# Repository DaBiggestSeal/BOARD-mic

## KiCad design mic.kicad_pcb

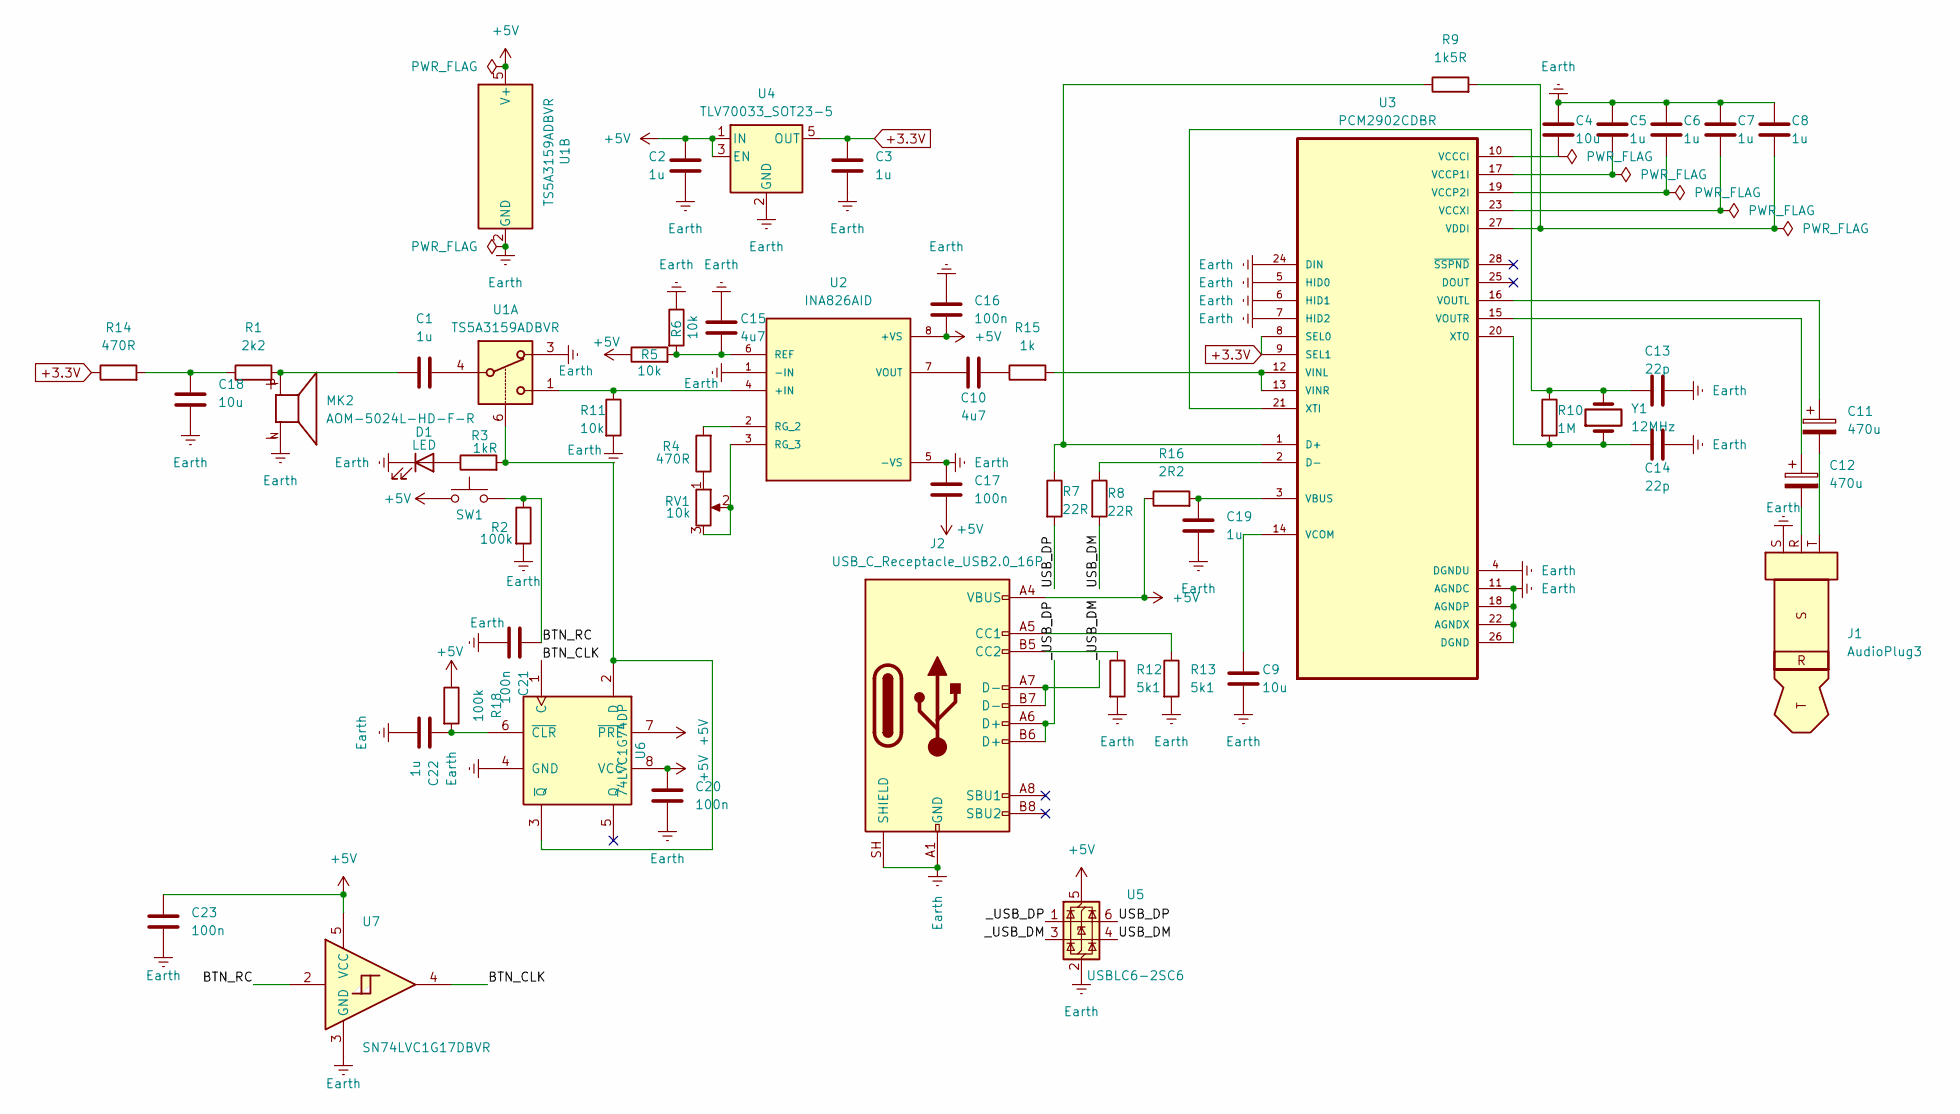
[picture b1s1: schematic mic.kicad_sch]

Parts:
C1, C2, C3, C5, C6, C7, C8, C19, C22: 1u; C_0603_1608Metric; LCSC C15849
C4, C9, C18: 10u; C_0603_1608Metric; LCSC C19702
C10, C15: 4u7; C_0603_1608Metric; LCSC C19666
C11, C12: 470u; CP_Elec_8x10; LCSC C2858857
C13, C14: 22p; C_0603_1608Metric; LCSC C1653
C16, C17, C20, C21, C23: 100n; C_0603_1608Metric; LCSC C149620
D1: LED; LED_D1.8mm_W1.8mm_H2.4mm_Horizontal_O1.27mm_Z1.6mm; LCSC C2917798
J1: AudioPlug3; Jack_3.5mm_KoreanHropartsElec_PJ-3920-3A_Vertical; LCSC C707259
J2: USB_C_Receptacle_USB2.0_16P; USB_C_Receptacle_G-Switch_GT-USB-7051x_NoA8; LCSC C2843970
MK2: AOM-5024L-HD-F-R; MIC_AOM-5024L-HD-F-R; PARTREV A; LCSC C3273730
R1: 2k2; R_0603_1608Metric; LCSC C4190
R2, R18: 100k; R_0603_1608Metric; LCSC C25803
R3: 1kR; R_0603_1608Metric; LCSC C22548
R4, R14: 470R; R_0603_1608Metric; LCSC C23179
R5, R6, R11: 10k; R_0603_1608Metric; LCSC C98220
R7, R8: 22R; R_0603_1608Metric; LCSC C23345
R9: 1k5R; R_0603_1608Metric; LCSC C22843
R10: 1M; R_0603_1608Metric; LCSC C22935
R12, R13: 5k1; R_0603_1608Metric; LCSC C23186
R15: 1k; R_0603_1608Metric; LCSC C22548
R16: 2R2; R_0603_1608Metric; LCSC C112307
RV1: 10k; Potentiometer_Alps_RK097_Single_Horizontal; LCSC C470577
SW1: SW_Push; SW_Tactile_SPST_Angled_PTS645Vx58-2LFS; LCSC alr C51018255
U1: TS5A3159ADBVR; SOT-23-6; LCSC C128405
U2: INA826AID; SOIC127P599X175-8N; PARTREV G; DigiKey_Part_Number 296-33294-5-ND
U3: PCM2902CDBR; SOP65P780X200-28N; DigiKey_Part_Number 2156-PCM2902CDBR-ND
U4: TLV70033_SOT23-5; SOT-23-5; LCSC C11337
U5: USBLC6-2SC6; SOT-23-6; LCSC C7519
U6: 74LVC1G74DP; TSSOP-8_3x3mm_P0.65mm; LCSC C548409
U7: SN74LVC1G17DBVR; SOT-23-5; LCSC C7836
Y1: 12MHz; Crystal_SMD_5032-2Pin_5.0x3.2mm; LCSC C112573

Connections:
+3.3V: C3.1, R14.1, U3.8 (SEL0), U3.9 (SEL1), U4.5 (OUT)
+5V: C2.2, C16.2, C17.2, C20.1, C23.1, J2.A4 (VBUS), J2.A9 (VBUS), J2.B4 (VBUS), J2.B9 (VBUS), R5.1, R16.1, R18.1, SW1.1, U1.5 (V+), U2.8 (+VS), U4.1 (IN), U4.3 (EN), U5.5 (VBUS), U6.7 (~PRE), U6.8 (VCC), U7.5 (VCC)
/BTN_CLK: U6.1 (C), U7.4
/BTN_RC: C21.1, R2.1, SW1.2, U7.2
/USB_DM: R8.2, U5.4 (I/O2)
/USB_DP: R7.2, U5.6 (I/O1)
/_USB_DM: J2.A7 (D-), J2.B7 (D-), U5.3 (I/O2)
/_USB_DP: J2.A6 (D+), J2.B6 (D+), U5.1 (I/O1)
Earth: C2.1, C3.2, C4.1, C5.1, C6.1, C7.1, C8.1, C9.2, C13.2, C14.2, C15.1, C16.1, C17.1, C18.2, C19.2, C20.2, C21.2, C22.2, C23.2, D1.1 (K), J1.S, J2.A1 (GND), J2.A12 (GND), J2.B1 (GND), J2.B12 (GND), J2.SH (SHIELD), MK2.N, R2.2, R6.1, R11.2, R12.2, R13.2, U1.2 (GND), U1.3, U2.1 (-IN), U2.5 (-VS), U3.4 (DGNDU), U3.5 (HID0), U3.6 (HID1), U3.7 (HID2), U3.11 (AGNDC), U3.18 (AGNDP), U3.22 (AGNDX), U3.24 (DIN), U3.26 (DGND), U4.2 (GND), U5.2 (GND), U6.4 (GND), U7.3 (GND)
unnamed: C1.1, MK2.P, R1.2
unnamed: C1.2, U1.4
unnamed: C10.1, R15.1
unnamed: C11.2, J1.T
unnamed: C12.2, J1.R
unnamed: C18.1, R1.1, R14.2
unnamed: D1.2 (A), R3.1
unnamed: J2.A5 (CC1), R13.1
unnamed: J2.B5 (CC2), R12.1
unnamed: R4.1, RV1.1
unnamed: R11.1, U1.1, U2.4 (+IN)
unnamed: C15.2, R5.2, R6.2, U2.6 (REF)
unnamed: R4.2, U2.2 (RG_2)
unnamed: RV1.2, RV1.3, U2.3 (RG_3)
unnamed: C10.2, U2.7 (VOUT)
unnamed: R7.1, R9.1, U3.1 (D+)
unnamed: R8.1, U3.2 (D-)
unnamed: C19.1, R16.2, U3.3 (VBUS)
unnamed: C4.2, U3.10 (VCCCI)
unnamed: C5.2, U3.17 (VCCP1I)
unnamed: C6.2, U3.19 (VCCP2I)
unnamed: C7.2, U3.23 (VCCXI)
unnamed: C9.1, U3.14 (VCOM)
unnamed: C8.2, R9.2, U3.27 (VDDI)
unnamed: R15.2, U3.12 (VINL), U3.13 (VINR)
unnamed: C11.1, U3.16 (VOUTL)
unnamed: C12.1, U3.15 (VOUTR)
unnamed: C13.1, R10.1, U3.21 (XTI), Y1.2
unnamed: C14.1, R10.2, U3.20 (XTO), Y1.1
unnamed: R3.2, U1.6, U6.2 (D), U6.3 (~Q)
unnamed: C22.1, R18.2, U6.6 (~CLR)

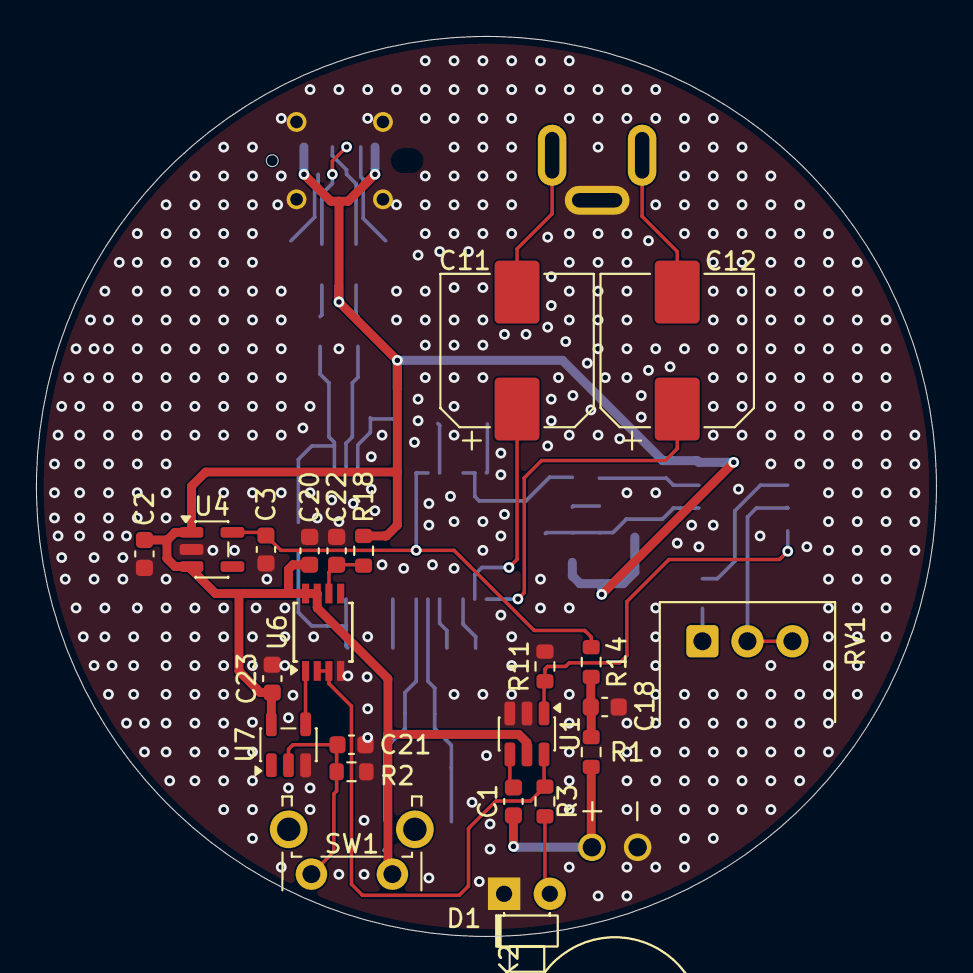
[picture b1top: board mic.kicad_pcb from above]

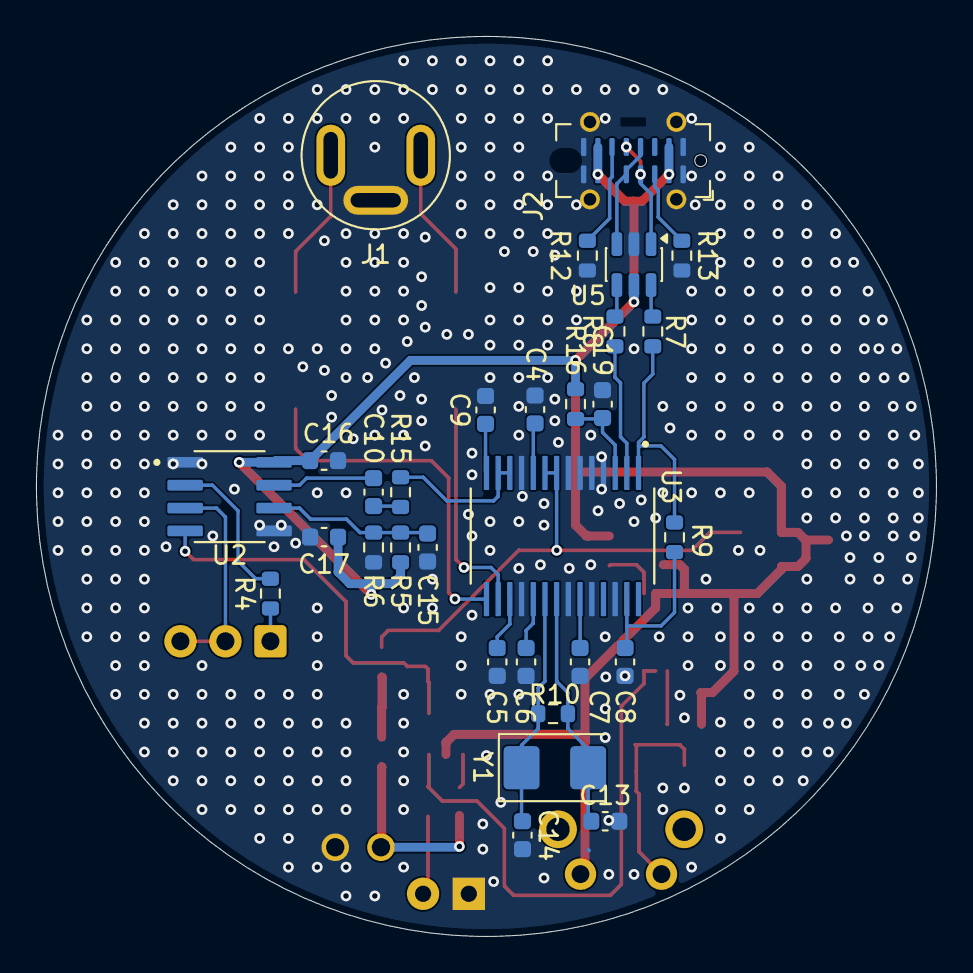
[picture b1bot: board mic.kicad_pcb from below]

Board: 2 copper layers, 50.0 x 50.0 mm, 54 parts (30 on the bottom side), 40 nets.
